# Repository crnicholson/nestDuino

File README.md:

# nestDuino

nestDuino is an Arduino kit designed to be soldered and assembled. This will hopefully teach the youth at New England Sci-Tech (NEST) more about electronics in the process of learning embedded engineering with Arduino. The kit is meant to be low cost and a drop-in replacement for the Arduino Uno, keeping all the same functionality, but with all through hole components, besides the AMS1117, for ease of assembly.

# License

nestDuino has no license. 

All rights reserved. Copyright New England Sci-Tech and Charles Nicholson 2024.

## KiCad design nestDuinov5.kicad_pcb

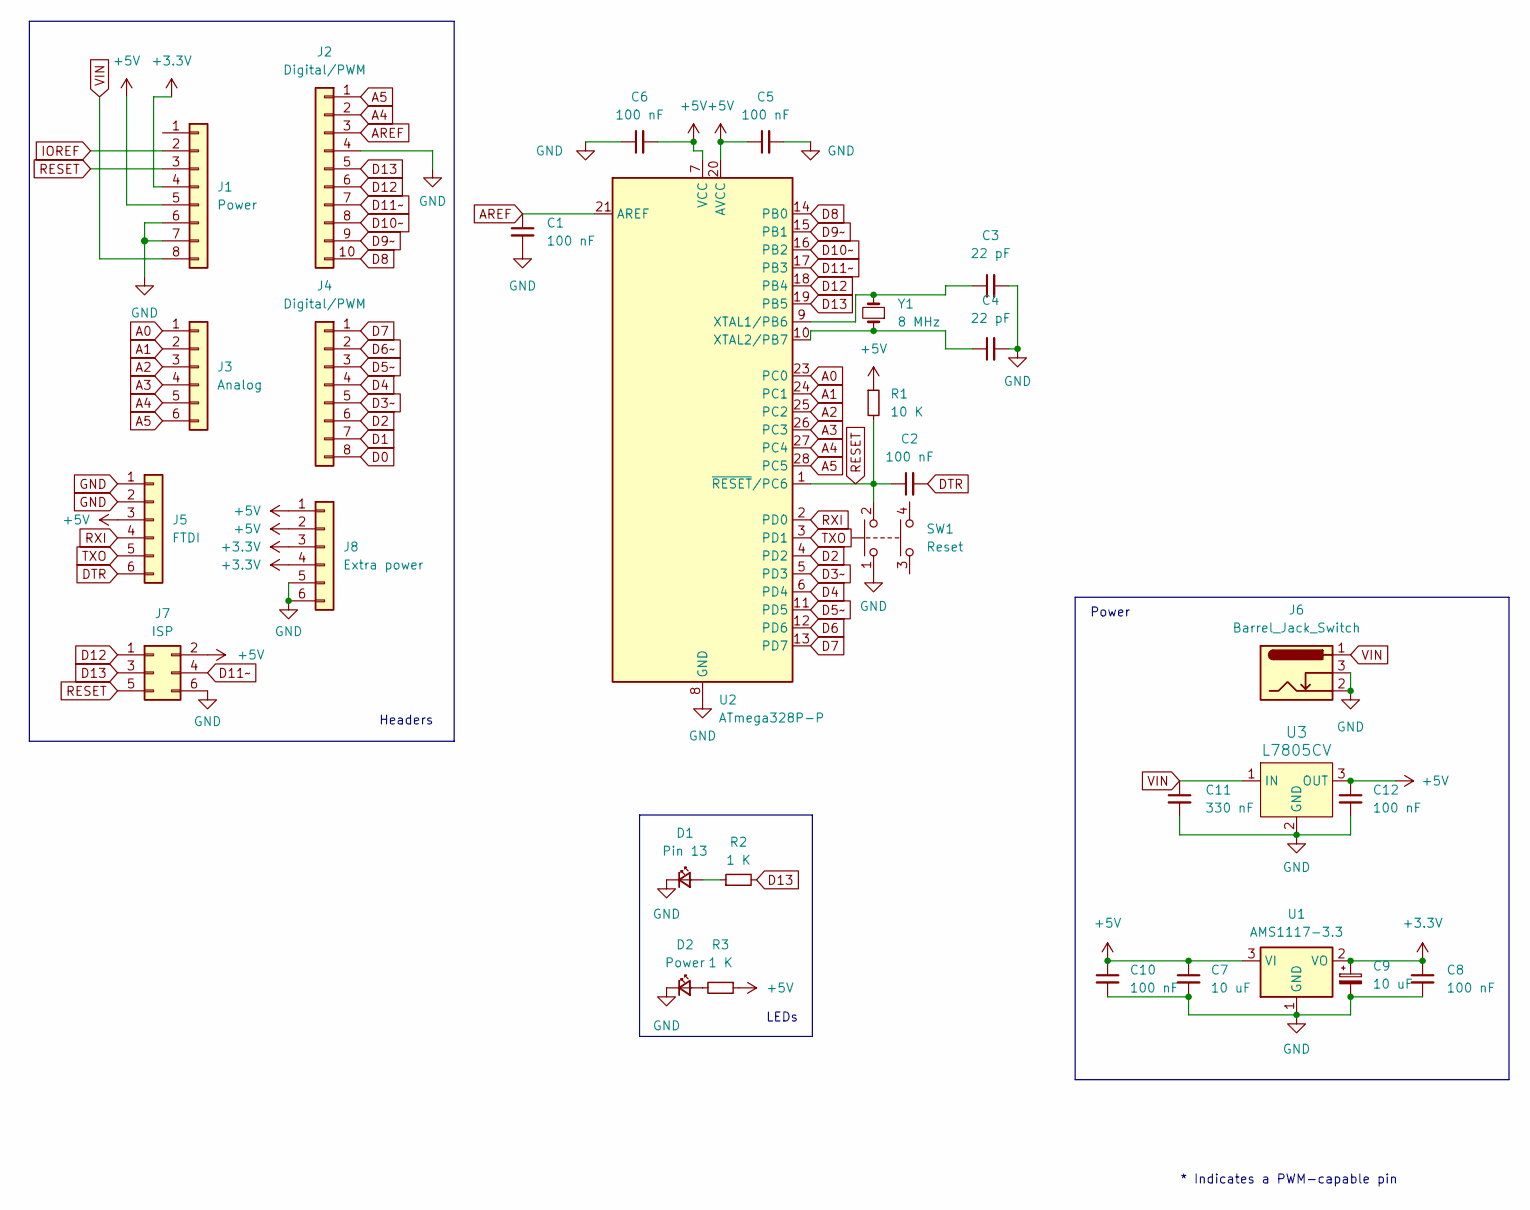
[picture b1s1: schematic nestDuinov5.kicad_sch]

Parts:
C1, C2, C5, C6, C8, C10, C12: 100 nF; C_Disc_D4.3mm_W1.9mm_P5.00mm
C3, C4: 22 pF; C_Disc_D4.3mm_W1.9mm_P5.00mm
C7: 10 uF; C_Disc_D4.3mm_W1.9mm_P5.00mm
C9: 10 uF; CP_Radial_D5.0mm_P2.00mm
C11: 330 nF; C_Disc_D4.3mm_W1.9mm_P5.00mm
D1: Pin 13; LED_D3.0mm
D2: Power; LED_D3.0mm
J1: Power; PinSocket_1x08_P2.54mm_Vertical
J2: Digital/PWM; PinSocket_1x10_P2.54mm_Vertical
J3: Analog; PinSocket_1x06_P2.54mm_Vertical
J4: Digital/PWM; PinSocket_1x08_P2.54mm_Vertical
J5: FTDI; PinSocket_1x06_P2.54mm_Horizontal
J6: Barrel_Jack_Switch; BarrelJack_Horizontal
J7: ISP; PinHeader_2x03_P2.54mm_Vertical
J8: Extra power; PinSocket_1x06_P2.54mm_Vertical
R1: 10 K; R_Axial_DIN0207_L6.3mm_D2.5mm_P10.16mm_Horizontal
R2, R3: 1 K; R_Axial_DIN0207_L6.3mm_D2.5mm_P10.16mm_Horizontal
SW1: Reset; SW_PUSH_6mm
U1: AMS1117-3.3; SOT-223-3_TabPin2
U2: ATmega328P-P; DIP-28_W7.62mm
U3: L7805CV; TO-220-3_Horizontal_TabDown; MPN L7805CV; Digi-Key_PN 497-1443-5-ND
Y1: 8 MHz; Crystal_HC49-U_Vertical

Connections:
+3.3V: C8.1, C9.1, J1.4, J8.3, J8.4, U1.2 (VO)
+5V: C5.1, C6.2, C7.1, C10.1, C12.1, J1.5, J5.3, J7.2, J8.1, J8.2, R1.1, R3.1, U1.3 (VI), U2.7 (VCC), U2.20 (AVCC), U3.3 (OUT)
A0: J3.1, U2.23 (PC0)
A1: J3.2, U2.24 (PC1)
A2: J3.3, U2.25 (PC2)
A3: J3.4, U2.26 (PC3)
A4: J2.2, J3.5, U2.27 (PC4)
A5: J2.1, J3.6, U2.28 (PC5)
AREF: C1.1, J2.3, U2.21 (AREF)
D0: J4.8
D1: J4.7
D2: J4.6, U2.4 (PD2)
D3~: J4.5, U2.5 (PD3)
D4: J4.4, U2.6 (PD4)
D5~: J4.3, U2.11 (PD5)
D6: U2.12 (PD6)
D6~: J4.2
D7: J4.1, U2.13 (PD7)
D8: J2.10, U2.14 (PB0)
D9~: J2.9, U2.15 (PB1)
D10~: J2.8, U2.16 (PB2)
D11~: J2.7, J7.4, U2.17 (PB3)
D12: J2.6, J7.1, U2.18 (PB4)
D13: J2.5, J7.3, R2.2, U2.19 (PB5)
DTR: C2.2, J5.6
GND: C1.2, C3.2, C4.2, C5.2, C6.1, C7.2, C8.2, C9.2, C10.2, C11.2, C12.2, D1.1 (K), D2.1 (K), J1.6, J1.7, J2.4, J5.1, J5.2, J6.2, J6.3, J7.6, J8.5, J8.6, SW1.1, U1.1 (GND), U2.8 (GND), U3.2 (GND)
IOREF: J1.2
unnamed: D1.2 (A), R2.1
unnamed: D2.2 (A), R3.2
unnamed: C3.1, U2.9 (XTAL1/PB6), Y1.2
unnamed: C4.1, U2.10 (XTAL2/PB7), Y1.1
RESET: C2.1, J1.3, J7.5, R1.2, SW1.2, U2.1 (~RESET/PC6)
RXI: J5.4, U2.2 (PD0)
TXO: J5.5, U2.3 (PD1)
VIN: C11.1, J1.8, J6.1, U3.1 (IN)

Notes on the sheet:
* Indicates a PWM-capable pin
Power
LEDs
Headers

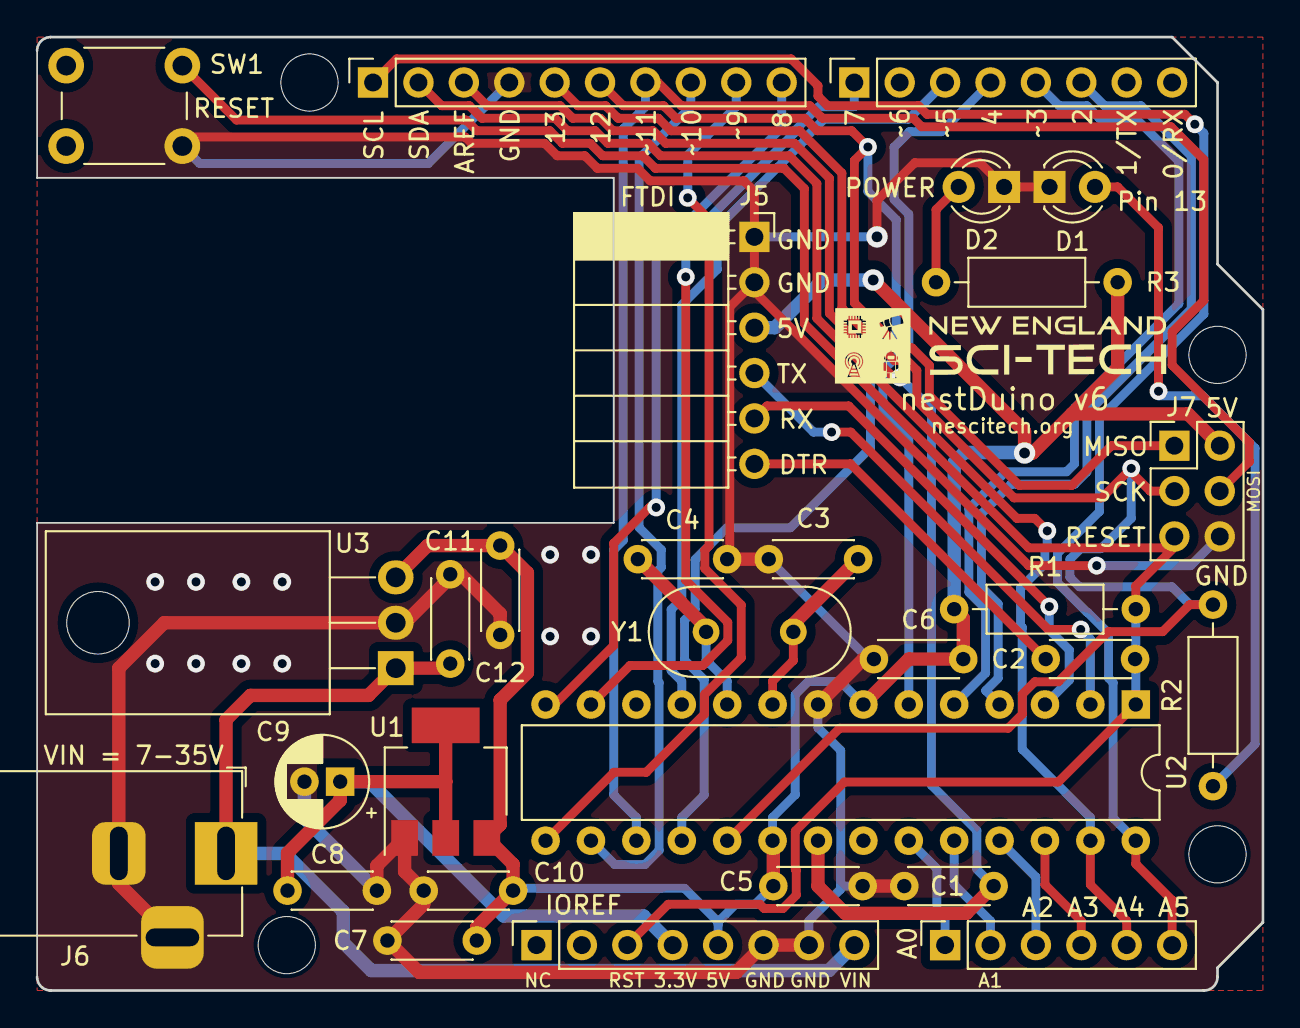
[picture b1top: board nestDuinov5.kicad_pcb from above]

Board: 2 copper layers, 68.6 x 53.3 mm, 33 parts (0 on the bottom side), 30 nets.

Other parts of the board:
MH1, MH2, MH3, MH4: MountingHole_3.2mm

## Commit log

2024-08-30 Edit README
